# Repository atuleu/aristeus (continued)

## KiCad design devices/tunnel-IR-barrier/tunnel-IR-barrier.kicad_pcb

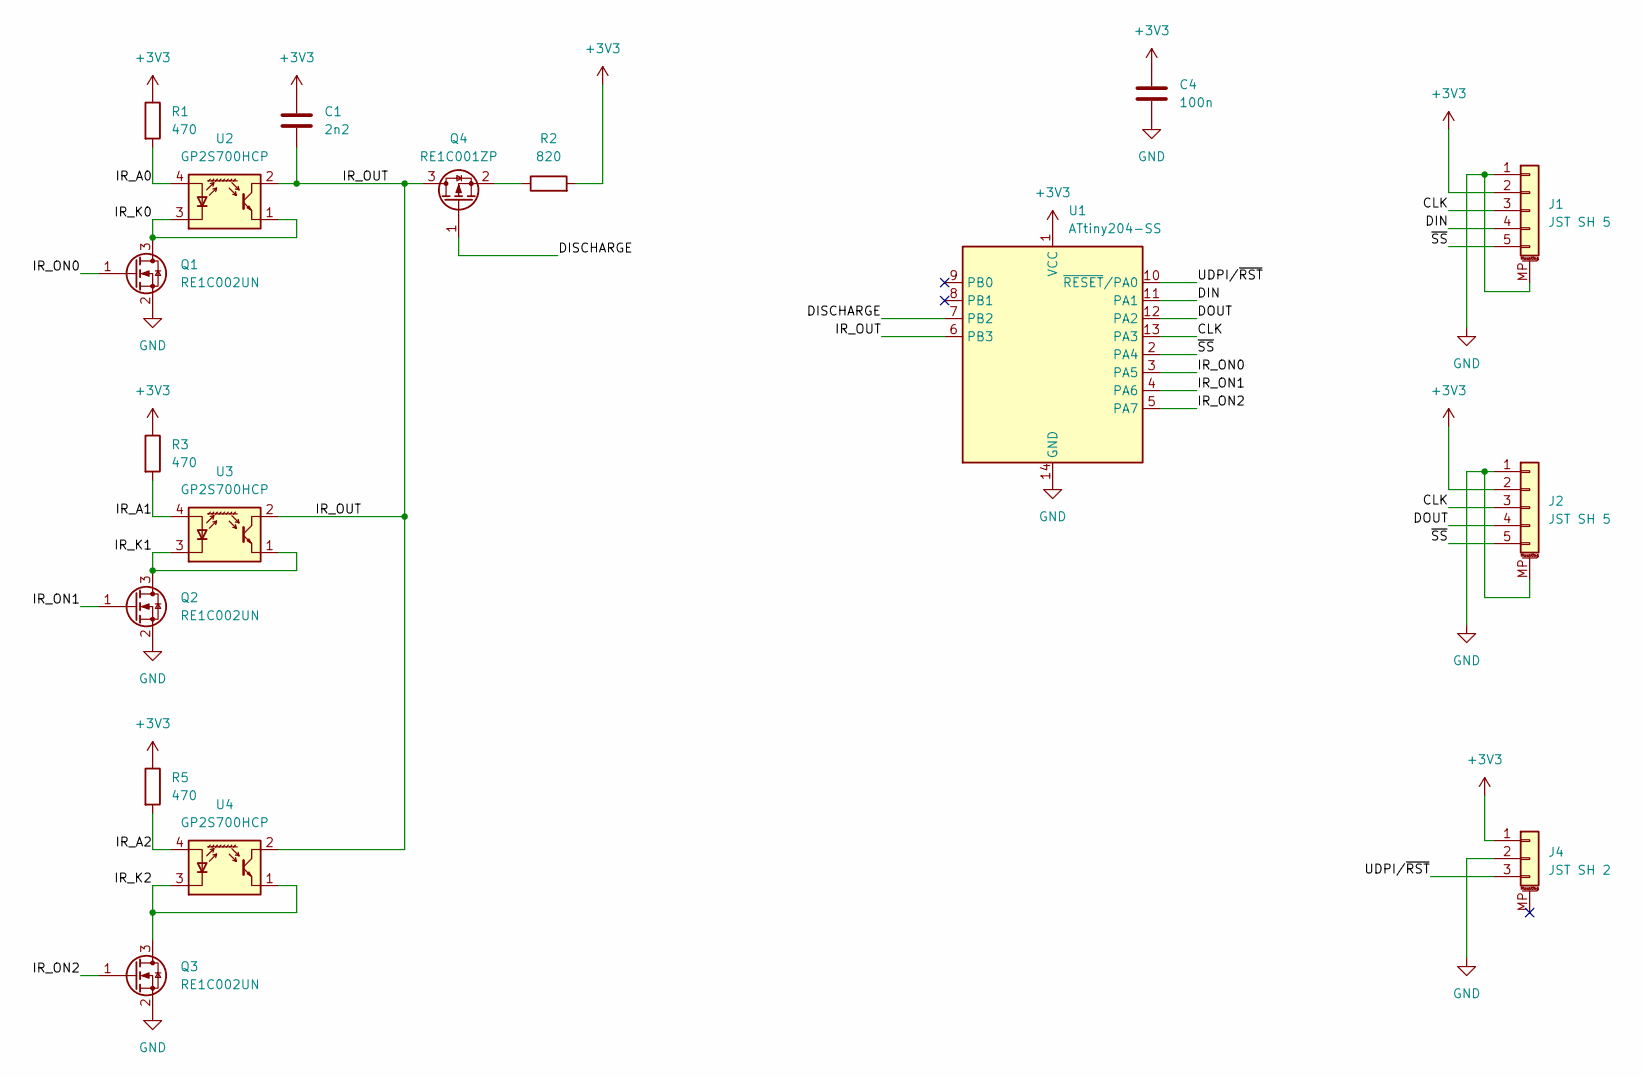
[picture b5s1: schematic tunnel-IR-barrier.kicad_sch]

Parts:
C1: 2n2; C_0603_1608Metric; MPN GRM1885C1H222JA01D
C4: 100n; C_0603_1608Metric; MPN CL10B104KB8NNWC
J1, J2: JST SH 5; JST_SH_BM05B-SRSS-TB_1x05-1MP_P1.00mm_Vertical; MPN SM05B-SRSS-TB
J4: JST SH 2; JST_SH_SM03B-SRSS-TB_1x03-1MP_P1.00mm_Horizontal; MPN SM03B-SRSS-TB
Q1, Q2, Q3: RE1C002UN; SOT-416; MPN RE1C002UN
Q4: RE1C001ZP; SOT-416; MPN RE1C001ZP
R1, R3, R5: 470; R_0603_1608Metric; MPN RC0603FR-07470RL
R2: 820; R_0603_1608Metric; MPN RC0603FR-07820RL
U1: ATtiny204-SS; SOIC-14_3.9x8.7mm_P1.27mm; MPN ATtiny204-SS
U2, U3, U4: GP2S700HCP; Sharp_GP2S700HCP; MPN GP2S700HCP

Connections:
+3V3: C1.1, C4.1, J1.2, J2.2, J4.1, R1.1, R2.2, R3.1, R5.1, U1.1 (VCC)
/CLK: J1.3, J2.3, U1.13 (PA3)
/DIN: J1.4, U1.11 (PA1)
/DISCHARGE: Q4.1 (G), U1.7 (PB2)
/DOUT: J2.4, U1.12 (PA2)
/IR_A0: R1.2, U2.4 (A)
/IR_A1: R3.2, U3.4 (A)
/IR_A2: R5.2, U4.4 (A)
/IR_K0: Q1.3 (D), U2.1, U2.3 (K)
/IR_K1: Q2.3 (D), U3.1, U3.3 (K)
/IR_K2: Q3.3 (D), U4.1, U4.3 (K)
/IR_ON0: Q1.1 (G), U1.3 (PA5)
/IR_ON1: Q2.1 (G), U1.4 (PA6)
/IR_ON2: Q3.1 (G), U1.5 (PA7)
/IR_OUT: C1.2, Q4.3 (D), U1.6 (PB3), U2.2, U3.2, U4.2
/UDPI/~RST: J4.3, U1.10 (~RESET/PA0)
/~SS: J1.5, J2.5, U1.2 (PA4)
GND: C4.2, J1.1, J1.MP (MountPin), J2.1, J2.MP (MountPin), J4.2, Q1.2 (S), Q2.2 (S), Q3.2 (S), U1.14 (GND)
unnamed: Q4.2 (S), R2.1

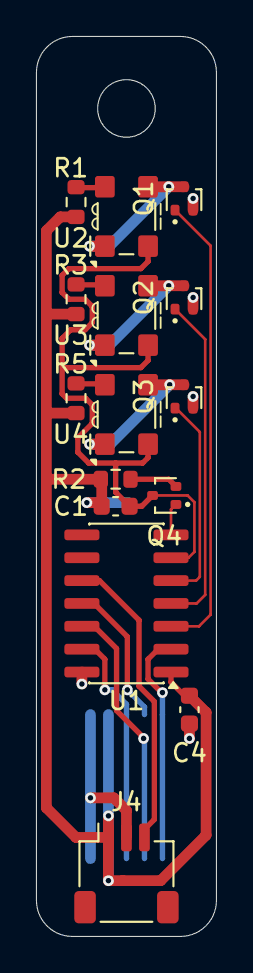
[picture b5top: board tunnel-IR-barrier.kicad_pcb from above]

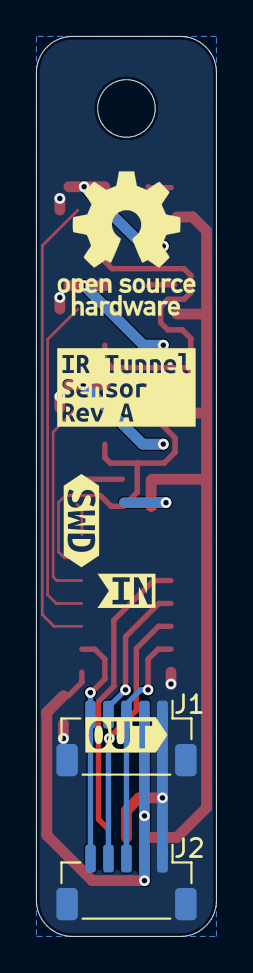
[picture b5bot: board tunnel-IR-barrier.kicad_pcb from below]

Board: 2 copper layers, 10.0 x 50.0 mm, 21 parts (6 on the bottom side), 19 nets.

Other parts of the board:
kibuzzard-6A22A01A: G***; kibuzzard-6A22A01A
kibuzzard-6A229D6B: G***; kibuzzard-6A229D6B
kibuzzard-6A229D11: G***; kibuzzard-6A229D11
kibuzzard-6A229D47: G***; kibuzzard-6A229D47

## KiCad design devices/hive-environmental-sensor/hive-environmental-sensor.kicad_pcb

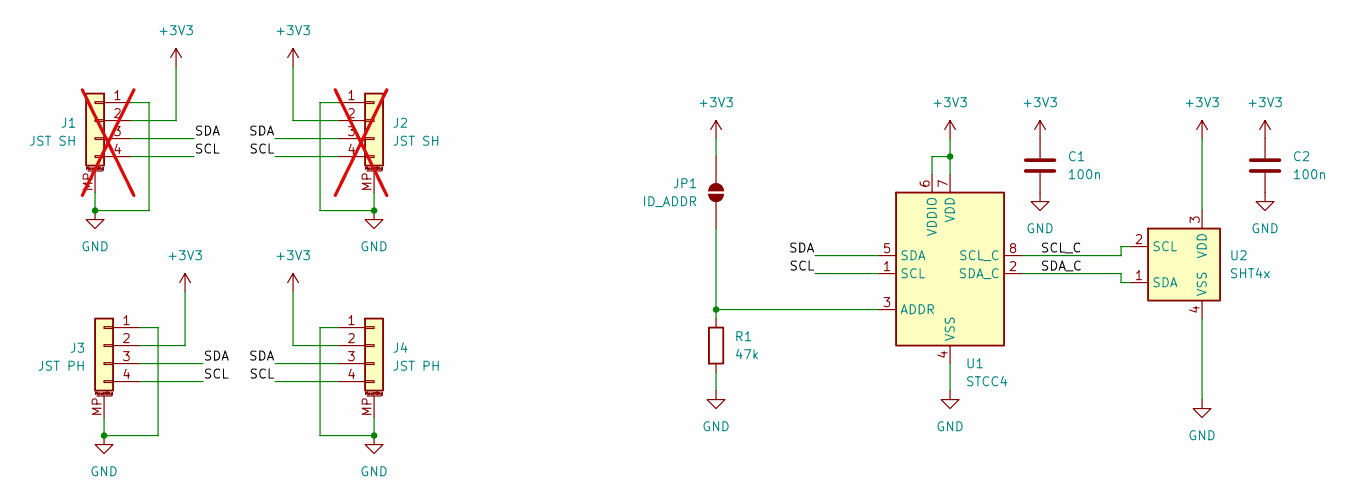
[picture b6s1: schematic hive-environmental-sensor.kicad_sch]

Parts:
C1, C2: 100n; C_0603_1608Metric
J1, J2: JST SH; JST_SH_SM04B-SRSS-TB_1x04-1MP_P1.00mm_Horizontal; not fitted
J3, J4: JST PH; JST_PH_S4B-PH-SM4-TB_1x04-1MP_P2.00mm_Horizontal
JP1: ID_ADDR; SolderJumper-2_P1.3mm_Open_RoundedPad1.0x1.5mm
R1: 47k; R_0603_1608Metric
U1: STCC4; Sensirion_STCC4_4x3_P1.15mm
U2: SHT4x; Sensirion_DFN-4_1.5x1.5mm_P0.8mm_SHT4x_NoCentralPad

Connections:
+3V3: C1.1, C2.1, J1.2, J2.2, J3.2, J4.2, JP1.2 (B), U1.6 (VDDIO), U1.7 (VDD), U2.3 (VDD)
/SCL: J1.4, J2.4, J3.4, J4.4, U1.1 (SCL)
/SCL_C: U1.8 (SCL_C), U2.2 (SCL)
/SDA: J1.3, J2.3, J3.3, J4.3, U1.5 (SDA)
/SDA_C: U1.2 (SDA_C), U2.1 (SDA)
GND: C1.2, C2.2, J1.1, J1.MP (MountPin), J2.1, J2.MP (MountPin), J3.1, J3.MP (MountPin), J4.1, J4.MP (MountPin), R1.2, U1.4 (VSS), U2.4 (VSS)
unnamed: JP1.1 (A), R1.1, U1.3 (ADDR)

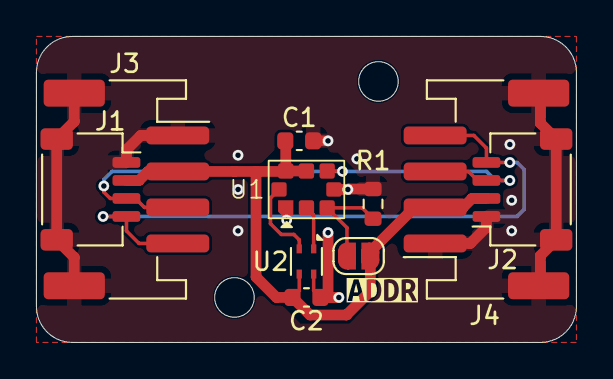
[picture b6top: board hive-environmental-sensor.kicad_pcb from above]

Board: 2 copper layers, 30.0 x 17.0 mm, 11 parts (0 on the bottom side), 7 nets.

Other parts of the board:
kibuzzard-6A0C40C0: G***; kibuzzard-6A0C40C0

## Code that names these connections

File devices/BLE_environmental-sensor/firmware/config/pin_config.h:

#ifndef PIN_CONFIG_H
#define PIN_CONFIG_H

// $[CMU]
// [CMU]$

// $[PRS.ASYNCH0]
// [PRS.ASYNCH0]$

// $[PRS.ASYNCH1]
// [PRS.ASYNCH1]$

// $[PRS.ASYNCH2]
// [PRS.ASYNCH2]$

// $[PRS.ASYNCH3]
// [PRS.ASYNCH3]$

// $[PRS.ASYNCH4]
// [PRS.ASYNCH4]$

// $[PRS.ASYNCH5]
// [PRS.ASYNCH5]$

// $[PRS.ASYNCH6]
// [PRS.ASYNCH6]$

// $[PRS.ASYNCH7]
// [PRS.ASYNCH7]$

// $[PRS.ASYNCH8]
// [PRS.ASYNCH8]$

// $[PRS.ASYNCH9]
// [PRS.ASYNCH9]$

// $[PRS.ASYNCH10]
// [PRS.ASYNCH10]$

// $[PRS.ASYNCH11]
// [PRS.ASYNCH11]$

// $[PRS.SYNCH0]
// [PRS.SYNCH0]$

// $[PRS.SYNCH1]
// [PRS.SYNCH1]$

// $[PRS.SYNCH2]
// [PRS.SYNCH2]$

// $[PRS.SYNCH3]
// [PRS.SYNCH3]$

// $[GPIO]
// [GPIO]$

// $[TIMER0]
// [TIMER0]$

// $[TIMER1]
// [TIMER1]$

// $[TIMER2]
// [TIMER2]$

// $[TIMER3]
// [TIMER3]$

// $[TIMER4]
// [TIMER4]$

// $[USART0]
// USART0 CLK on PC01
#ifndef USART0_CLK_PORT                         
#define USART0_CLK_PORT                          SL_GPIO_PORT_C
#endif
#ifndef USART0_CLK_PIN                          
#define USART0_CLK_PIN                           1
#endif

// USART0 CS on PC03
#ifndef USART0_CS_PORT                          
#define USART0_CS_PORT                           SL_GPIO_PORT_C
#endif
#ifndef USART0_CS_PIN                           
#define USART0_CS_PIN                            3
#endif

// USART0 RX on PC02
#ifndef USART0_RX_PORT                          
#define USART0_RX_PORT                           SL_GPIO_PORT_C
#endif
#ifndef USART0_RX_PIN                           
#define USART0_RX_PIN                            2
#endif

// USART0 TX on PC00
#ifndef USART0_TX_PORT                          
#define USART0_TX_PORT                           SL_GPIO_PORT_C
#endif
#ifndef USART0_TX_PIN                           
#define USART0_TX_PIN                            0
#endif

// [USART0]$

// $[USART1]
// [USART1]$

// $[I2C1]
// [I2C1]$

// $[PDM]
// [PDM]$

// $[LETIMER0]
// [LETIMER0]$

// $[IADC0]
// [IADC0]$

// $[I2C0]
// I2C0 SCL on PB03
#ifndef I2C0_SCL_PORT                           
#define I2C0_SCL_PORT                            SL_GPIO_PORT_B
#endif
#ifndef I2C0_SCL_PIN                            
#define I2C0_SCL_PIN                             3
#endif

// I2C0 SDA on PB04
#ifndef I2C0_SDA_PORT                           
#define I2C0_SDA_PORT                            SL_GPIO_PORT_B
#endif
#ifndef I2C0_SDA_PIN                            
#define I2C0_SDA_PIN                             4
#endif

// [I2C0]$

// $[EUART0]
// EUART0 RX on PA06
#ifndef EUART0_RX_PORT                          
#define EUART0_RX_PORT                           SL_GPIO_PORT_A
#endif
#ifndef EUART0_RX_PIN                           
#define EUART0_RX_PIN                            6
#endif

// EUART0 TX on PA05
#ifndef EUART0_TX_PORT                          
#define EUART0_TX_PORT                           SL_GPIO_PORT_A
#endif
#ifndef EUART0_TX_PIN                           
#define EUART0_TX_PIN                            5
#endif

// [EUART0]$

// $[PTI]
// PTI DFRAME on PC05
#ifndef PTI_DFRAME_PORT                         
#define PTI_DFRAME_PORT                          SL_GPIO_PORT_C
#endif
#ifndef PTI_DFRAME_PIN                          
#define PTI_DFRAME_PIN                           5
#endif

// PTI DOUT on PC04
#ifndef PTI_DOUT_PORT                           
#define PTI_DOUT_PORT                            SL_GPIO_PORT_C
#endif
#ifndef PTI_DOUT_PIN                            
#define PTI_DOUT_PIN                             4
#endif

// [PTI]$

// $[MODEM]
// [MODEM]$

// $[CUSTOM_PIN_NAME]
#ifndef _PORT                                   
#define _PORT                                    SL_GPIO_PORT_A
#endif
#ifndef _PIN                                    
#define _PIN                                     0
#endif










#ifndef LPS22HH_INT_PORT                        
#define LPS22HH_INT_PORT                         SL_GPIO_PORT_B
#endif
#ifndef LPS22HH_INT_PIN                         
#define LPS22HH_INT_PIN                          1
#endif














// [CUSTOM_PIN_NAME]$


#endif // PIN_CONFIG_H

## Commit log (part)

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2026-05-11 First version with rp2040
2026-05-11 Uses RP2354A instead of RP2040 It simplifies the BOM a lot, and removes an hard to solder component
2026-05-13 Uses a Ferrite bead for Power Line Filtering.
2026-05-19 Adds OSHW strong license
2026-05-19 Restructure repo for multiple Hardware project
2026-05-19 Updates structure of the project.
2026-05-19 Fixes models from library
2026-05-19 Finally makes the layout for ECAD fiule simpler
2026-05-19 Adds Raspberry Pi uHAT for Fan & QWIIC
2026-05-19 Adds Sensor board
2026-05-22 Adds a tunnel barrier device
2026-05-23 Improves the input filter of the LED driver (no self-excitation)
2026-05-26 Adds missing links
2026-05-26 Improves input filter for LED driver
2026-06-08 Update IR barrier for easier firmware implementation
    Uses a common readout circuitry, and a high-side switch to not have to switch pin direction with interupts
2026-06-08 !fixup
2026-06-08 [rpi-uHAT] Adds MPN for all parts.
2026-06-24 [wip] Adds a BLE IoT sensor for temperature humidity pressure and Co2
2026-06-25 [wip] More stuff
